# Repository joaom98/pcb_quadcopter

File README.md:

# pcb_quadcopter
An open-source PCB multirotor project, development in progress.
The intent is to make an affordable, simple and customizable quadcopter that can be built and used by anyone. 

## Inspiration

So, I have seen some interesting projects online and decided to try developing a variation. Here are some of the references that inspired me into making my own:

* [Arduino PCB quadcopter - ElecttoNOOBS](https://www.youtube.com/watch?v=J0x4ChjUS00)
* [ArduBee, a Ready-To-Fly Micro drone for Education and Swarming](https://discuss.ardupilot.org/t/ardubee-a-ready-to-fly-micro-drone-for-education-and-swarming/54362)
* [Microhawk at Outcast Dronework - Rotor Riot](https://www.youtube.com/watch?v=aRctXEhmRdY)
* [MultiWii](http://www.multiwii.com/)
* [OpenFC Open Hardware Flight Controller - DroneMesh](https://www.youtube.com/playlist?list=PLoPtpxJIxgnYnPrOeGHs3rdhhPgNGIYN5)
* [FeatherWing quadcopter](https://hackaday.io/project/168441-quadcopter-featherwing-for-huzzah32)

## Specifications

Here are some of the specifications that I want to follow for this project. They are open to changes:

* PCB Frame containing all of the electronics and components
* STM32 microcontroller able to run BetaFlight
* 7mm brushed motors
* 2" Propellers
* Micro RF SBUS receiver
* 18650 Li-Ion batteries

## Future implementations/extras

Theese are some features that are cool but aren't included in the base project (yet, hopefully):

* FPV camera and VTX
* SD card for camera footage
* RPi 0 support
* Ardupilot support

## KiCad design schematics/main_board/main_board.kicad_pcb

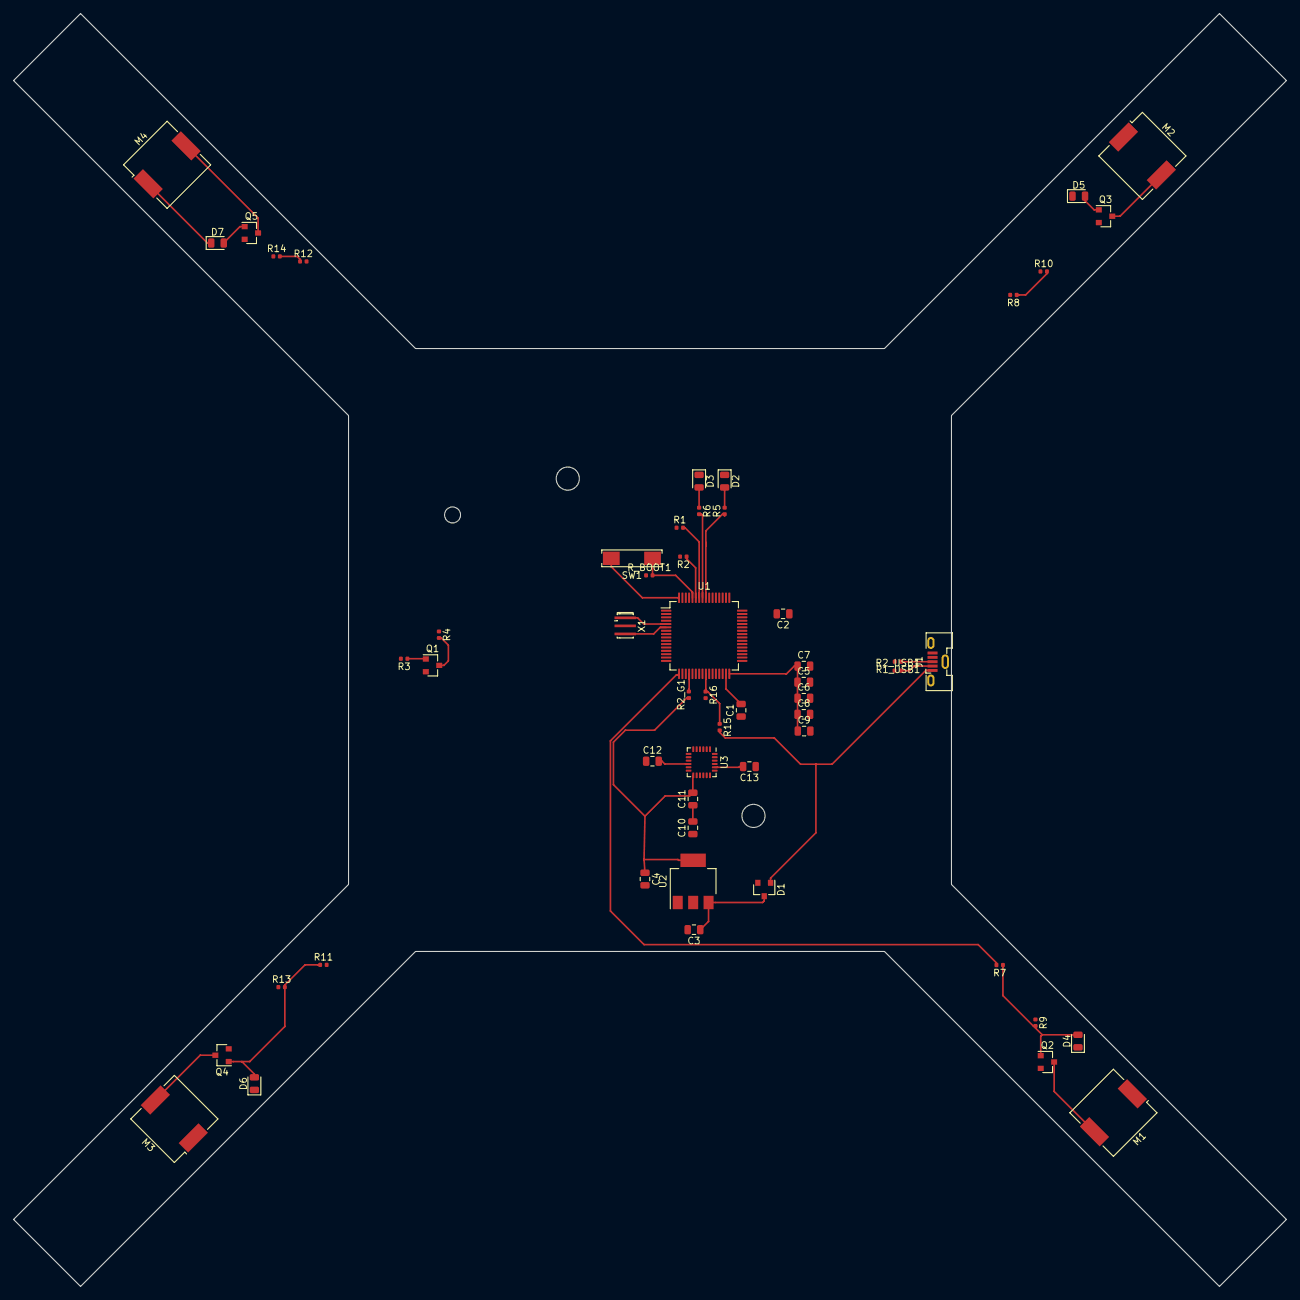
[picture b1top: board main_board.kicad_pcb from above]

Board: 2 copper layers, 190.0 x 190.0 mm, 56 parts (1 on the bottom side), 43 nets.

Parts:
BT1: Battery_Cell; BatteryHolder_Keystone_1042_1x18650
C1, C2, C5, C6, C7, C8, C9: 100nF; C_0805_2012Metric
C3, C4: 10uF; C_0805_2012Metric
C10: 1uF; C_0805_2012Metric
C11, C12: 0.1uF; C_0805_2012Metric
C13: 2.2nF; C_0805_2012Metric
D1: BAT54C; SOT-23
D2, D3: LED; LED_0805_2012Metric
D4, D5, D6, D7: D_Schottky; D_0805_2012Metric
J1: USB_B_Micro; USB_Micro-B_Molex-105133-0031
M1, M2, M3, M4: Motor_DC; Buzzer_CUI_CPT-9019S-SMT
Q1: BC817; SOT-23
Q2, Q3, Q4, Q5: 2N7002; SOT-23
R1, R2, R2_G1, R15, R16: 10k; R_0402_1005Metric
R1_USB1, R2_USB1: 22; R_0402_1005Metric
R3, R4: R; R_0402_1005Metric
R5, R6: 1K; R_0402_1005Metric
R7, R8, R11, R12: 100; R_0402_1005Metric
R9, R10, R13, R14: 10K; R_0402_1005Metric
R_BOOT1: 10k; R_0402_1005Metric
SW1: SW_DIP_x01; SW_SPST_REED_CT05-XXXX-J1
U1: STM32F405RGTx; LQFP-64_10x10mm_P0.5mm
U2: NCP1117-1.5_SOT223; SOT-223-3_TabPin2
U3: MPU-6000; InvenSense_QFN-24_4x4mm_P0.5mm
X1: Resonator 8MHz; Resonator_SMD_muRata_CSTxExxV-3Pin_3.0x1.1mm_HandSoldering

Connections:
5V_USB: D1.1, J1.1, R15.2
BAT+: BT1.1, D1.2, D4.1, D5.1, D6.1, D7.1, M1.1, M2.1, M3.1, M4.1, R4.1, U1.9
GND: BT1.2, C1.1, C2.1, C3.2, C4.2, C5.2, C6.2, C7.2, C8.2, C9.2, C10.1, C12.1, C13.1, D2.1, D3.1, J1.5, Q1.2, Q2.2, Q3.2, Q4.2, Q5.2, R9.1, R10.1, R13.1, R14.1, R16.2, R_BOOT1.1, U2.1, U3.1, U3.11, U3.18, X1.2
GYRO_CS: R2_G1.2, U1.20, U3.8
GYRO_INT: U1.24, U3.12
GYRO_SCL: U1.21, U3.23
GYRO_SDA: U1.23, U3.24
GYRO_SDO: U1.22, U3.9
LED1: R5.1, U1.56
LED2: R6.2, U1.57
unnamed: C1.2, U1.31
unnamed: C2.2, U1.47
unnamed: C3.1, D1.3, U2.3
unnamed: C10.2, C11.1
unnamed: C12.2, U3.10
unnamed: C13.2, U3.20
unnamed: D2.2, R5.2
unnamed: D3.2, R6.1
unnamed: D4.2, Q2.1, R7.1, R9.2
unnamed: D5.2, Q3.1, R8.1, R10.2
unnamed: D6.2, Q4.1, R11.1, R13.2
unnamed: D7.2, Q5.1, R12.1, R14.2
unnamed: J1.2, R2_USB1.2
unnamed: J1.3, R1_USB1.1
unnamed: M1.2, Q2.3
unnamed: M2.2, Q3.3
unnamed: M3.2, Q4.3
unnamed: M4.2, Q5.3
unnamed: Q1.1, R3.1
unnamed: R1.2, U1.58
unnamed: R1_USB1.2, U1.45
unnamed: R2.1, U1.59
unnamed: R2_USB1.1, U1.44
unnamed: R15.1, R16.1, U1.25
unnamed: R_BOOT1.2, SW1.2, U1.60
unnamed: U1.5, X1.1
unnamed: U1.6, X1.3
S1: R7.2, U1.17
S2: R8.2, U1.26
S3: R11.2, U1.27
S4: R12.2, U1.16
UART1_RX: Q1.3, R4.2, U1.43
VCC: C4.1, C5.1, C6.1, C7.1, C8.1, C9.1, C11.2, R2_G1.1, SW1.1, U1.1, U1.32, U1.48, U1.64, U2.2, U3.13

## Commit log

2020-04-18 Updated README with requirements and some info
2020-04-18 Fixed typo
2020-04-18 Added extras in the README
2020-04-18 Folder with boards created
2020-04-18 Added main uC and Gyro schematics
2020-04-18 Saved changes
2020-04-19 Added motors, voltage regulator and LED's
2020-04-19 Updating cache
2020-04-20 Created the PCB frame and added the components on top
2020-04-21 no idea what this file is
2020-04-27 Changed some footprints, added some traces
2020-04-27 Fixed oscillator footprint and motor signal names
2020-06-22 Added featherwing project to sources in the readme
